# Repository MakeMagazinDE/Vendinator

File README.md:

Maker Media GmbH

***

# Verkaufsautomat mit ESP

### Eigene Waren zu vertreiben, kann ganz schön aufwendig sein. Mit einem selbst gebauten Automaten geht das ganz einfach. Einmal eingestellt, übernimmt er die Transaktionen und meldet Verkäufe und Fehler ans Smartphone. Man muss sich nur gut überlegen, wie Hard- und Software zusammenspielen sollen. Dann lässt sich sogar im Schlaf Geld verdienen.

Ergänzend zum Artikel in der Make 5/24 findet ihr hier die Sketches, Schaltpläne und Ablaufpläne.

Den vollständigen Artikel kann man in der **[Make-Ausgabe 5/24](https://www.heise.de/select/make/2024/5)** lesen.

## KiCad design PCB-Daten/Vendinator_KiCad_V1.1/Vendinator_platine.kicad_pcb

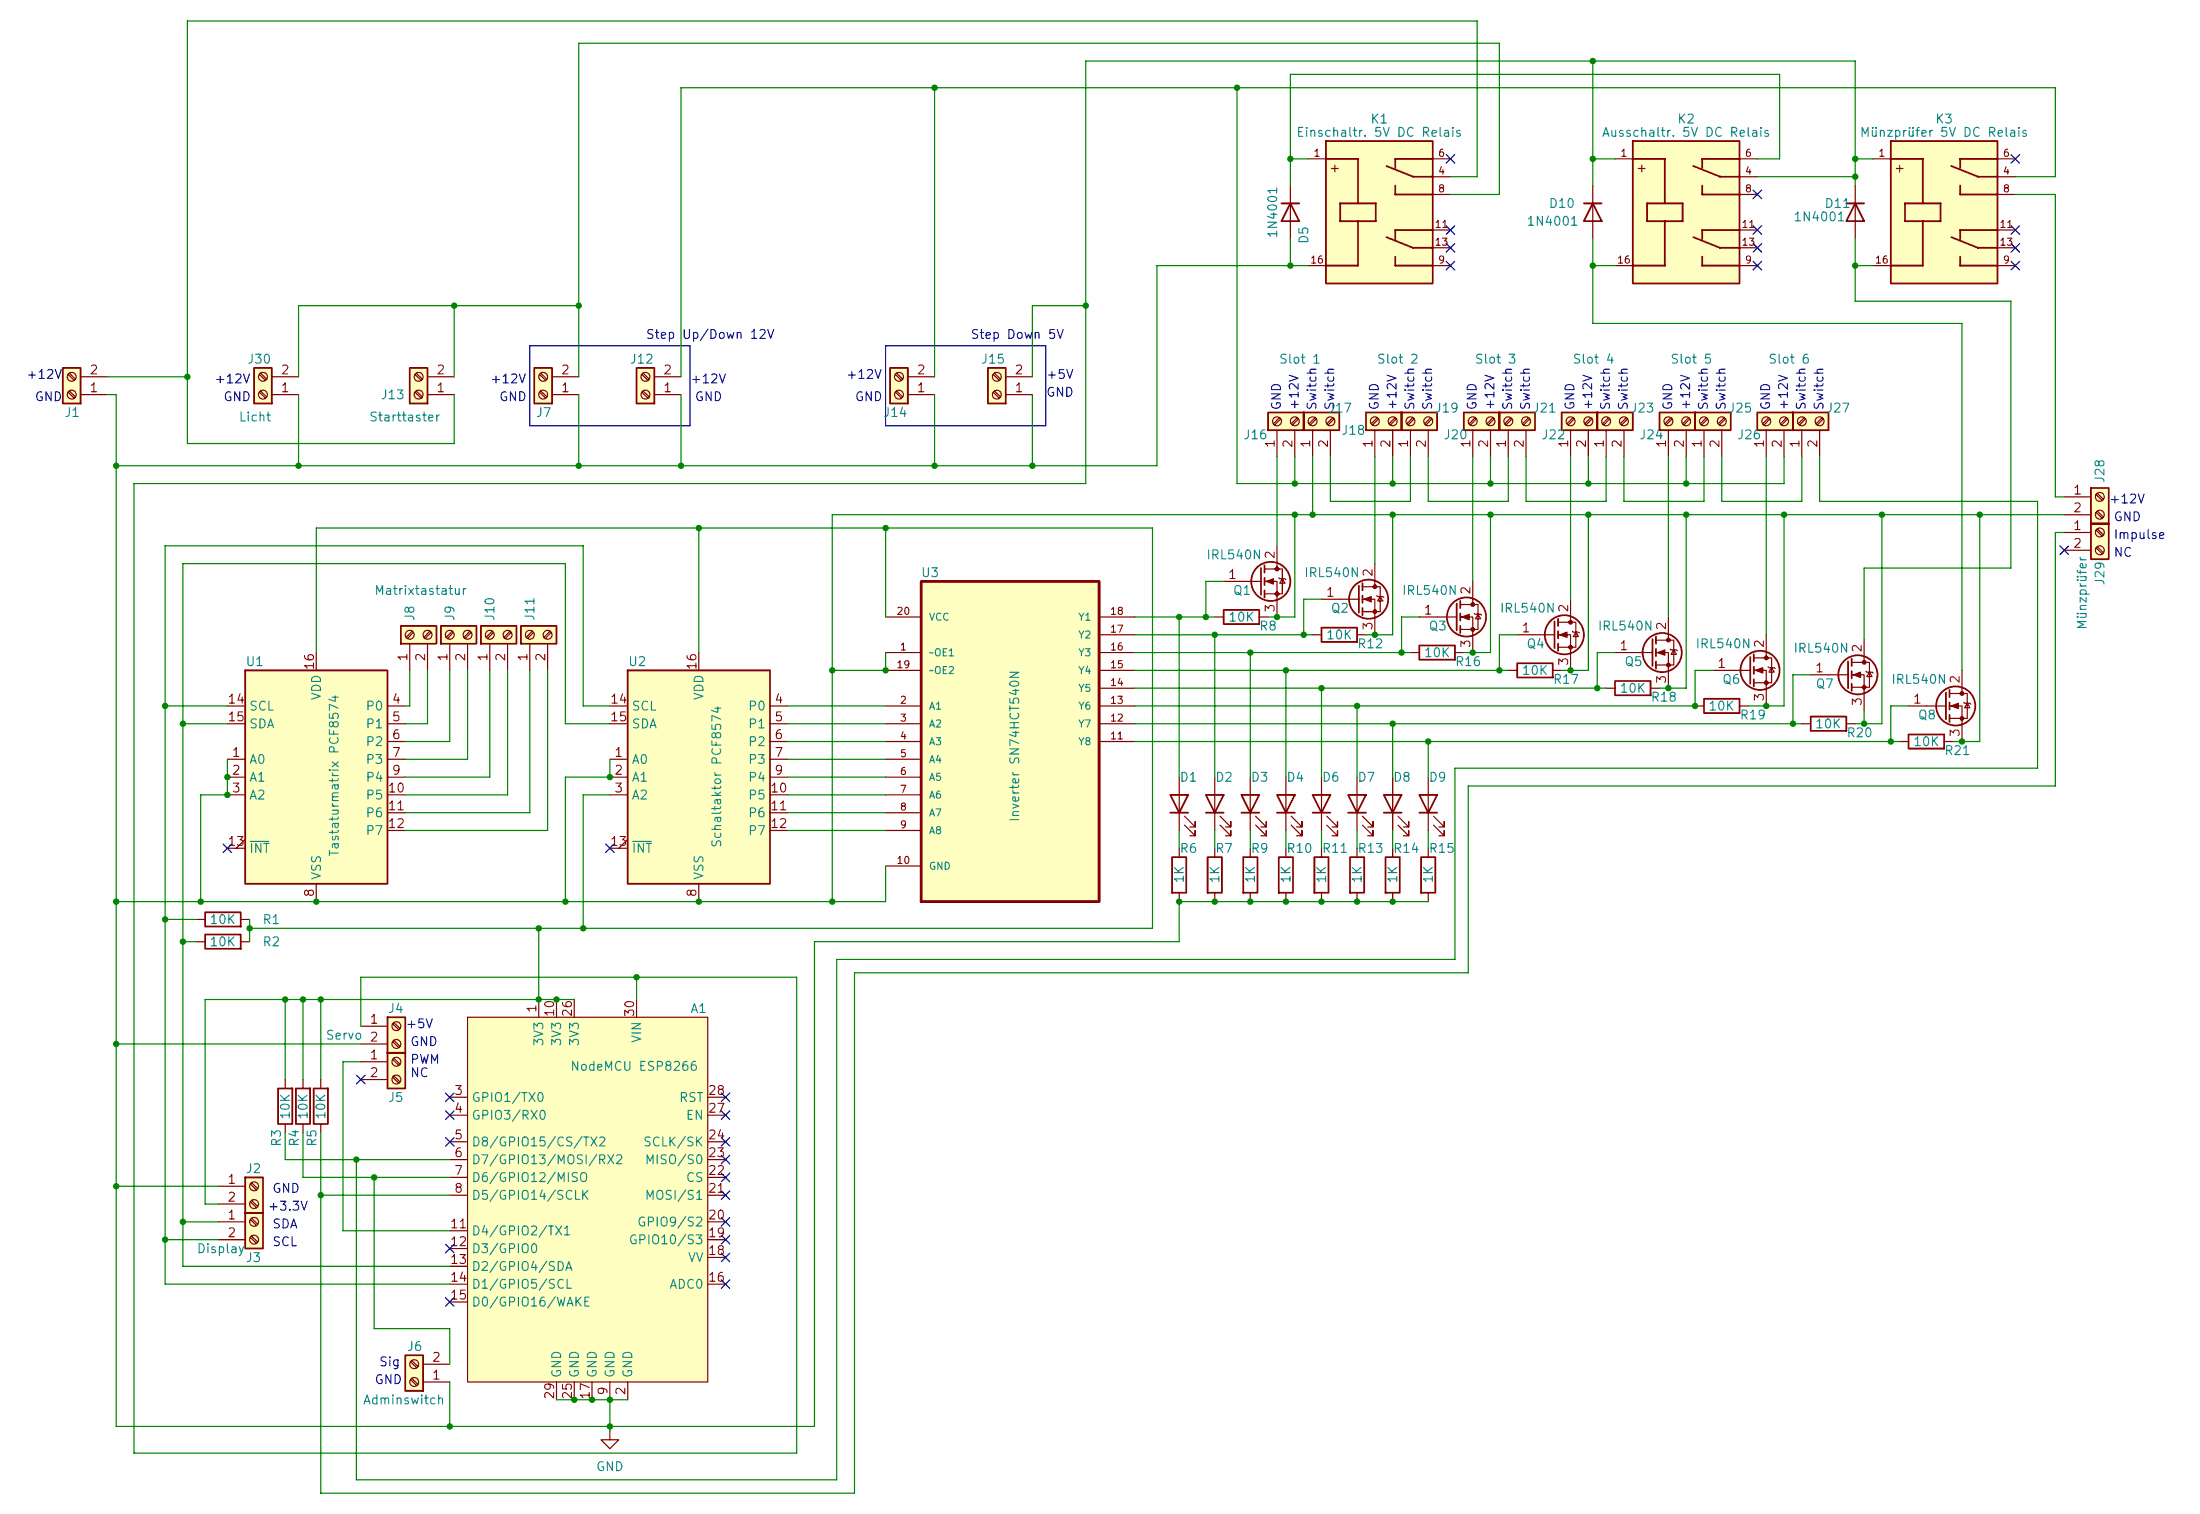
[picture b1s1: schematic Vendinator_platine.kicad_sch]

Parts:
A1: NodeMCU ESP8266; NodeMCU-LoLinV3_2
D1: LED grün; LED_D5.0mm
D2, D3, D4, D6, D7, D8, D9: LED; LED_D5.0mm
D5, D10, D11: 1N4001; D_DO-41_SOD81_P10.16mm_Horizontal
J1: Batterie IN; TerminalBlock_MetzConnect_Type011_RT05502HBWC_1x02_P5.00mm_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
J2: Display; TerminalBlock_MetzConnect_Type011_RT05502HBWC_1x02_P5.00mm_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
J3: Display 2; TerminalBlock_MetzConnect_Type011_RT05502HBWC_1x02_P5.00mm_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
J4: Servo; TerminalBlock_MetzConnect_Type011_RT05502HBWC_1x02_P5.00mm_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
J5: Servo 2; TerminalBlock_MetzConnect_Type011_RT05502HBWC_1x02_P5.00mm_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
J6: Adminswitch; TerminalBlock_MetzConnect_Type011_RT05502HBWC_1x02_P5.00mm_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
J7: 12V Step Up/Down IN; JUP_P20mm
J8: Matrixtastatur; TerminalBlock_MetzConnect_Type011_RT05502HBWC_1x02_P5.00mm_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
J9: Matrixtastatur 2; TerminalBlock_MetzConnect_Type011_RT05502HBWC_1x02_P5.00mm_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
J10: Matrixtastatur 3; TerminalBlock_MetzConnect_Type011_RT05502HBWC_1x02_P5.00mm_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
J11: Matrixtastatur 4; TerminalBlock_MetzConnect_Type011_RT05502HBWC_1x02_P5.00mm_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
J12: 12V Step Up/Down OUT; JUP_P20mm
J13: Starttaster; TerminalBlock_MetzConnect_Type011_RT05502HBWC_1x02_P5.00mm_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
J14: Step Down 5V IN; JUP_P20mm
J15: Step Down 5V OUT; JUP_P20mm
J16: Slot 1; TerminalBlock_MetzConnect_Type011_RT05502HBWC_1x02_P5.00mm_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
J17: Slotswitch 1; TerminalBlock_MetzConnect_Type011_RT05502HBWC_1x02_P5.00mm_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
J18: Slot 2; TerminalBlock_MetzConnect_Type011_RT05502HBWC_1x02_P5.00mm_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
J19: Slotswitch 2; TerminalBlock_MetzConnect_Type011_RT05502HBWC_1x02_P5.00mm_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
J20: Slot 3; TerminalBlock_MetzConnect_Type011_RT05502HBWC_1x02_P5.00mm_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
J21: Slotswitch 3; TerminalBlock_MetzConnect_Type011_RT05502HBWC_1x02_P5.00mm_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
J22: Slot 4; TerminalBlock_MetzConnect_Type011_RT05502HBWC_1x02_P5.00mm_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
J23: Slotswitch 4; TerminalBlock_MetzConnect_Type011_RT05502HBWC_1x02_P5.00mm_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
J24: Slot 5; TerminalBlock_MetzConnect_Type011_RT05502HBWC_1x02_P5.00mm_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
J25: Slotswitch 5; TerminalBlock_MetzConnect_Type011_RT05502HBWC_1x02_P5.00mm_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
J26: Slot 6; TerminalBlock_MetzConnect_Type011_RT05502HBWC_1x02_P5.00mm_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
J27: Slotswitch 6; TerminalBlock_MetzConnect_Type011_RT05502HBWC_1x02_P5.00mm_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
J28: Münzprüfer; TerminalBlock_MetzConnect_Type011_RT05502HBWC_1x02_P5.00mm_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
J29: Münzprüfer 2; TerminalBlock_MetzConnect_Type011_RT05502HBWC_1x02_P5.00mm_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
J30: Licht; TerminalBlock_MetzConnect_Type011_RT05502HBWC_1x02_P5.00mm_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
K1: Einschaltr. 5V DC Relais; SDS_Relay; PARTREV 0917
K2: Ausschaltr. 5V DC Relais; SDS_Relay; PARTREV 0917
K3: Münzprüfer 5V DC Relais; SDS_Relay; PARTREV 0917
Q1, Q2, Q3, Q4, Q5, Q6, Q7, Q8: IRL540N; TO-220-3_Vertical
R1, R2, R3, R4, R5, R8, R12, R16, R17, R18, R19, R20, R21: 10K; R_Axial_DIN0207_L6.3mm_D2.5mm_P10.16mm_Horizontal
R6, R7, R9, R10, R11, R13, R14, R15: 1K; R_Axial_DIN0207_L6.3mm_D2.5mm_P10.16mm_Horizontal
U1: Tastaturmatrix PCF8574; DIP-16_W7.62mm_Socket_LongPads
U2: Schaltaktor PCF8574; DIP-16_W7.62mm_Socket_LongPads
U3: Inverter SN74HCT540N; DIP-20_W7.62mm_Socket_LongPads; MPN SN74HCT540N

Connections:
GND: A1.2 (GND), A1.9 (GND), A1.17 (GND), A1.25 (GND), A1.29 (GND), D5.2 (A), J1.1, J2.1, J4.2, J6.1, J7.1, J12.1, J14.1, J15.1, J17.1, J28.2, J30.1, K1.16, Q1.3 (S), Q2.3 (S), Q3.3 (S), Q4.3 (S), Q5.3 (S), Q6.3 (S), Q7.3 (S), Q8.3 (S), R6.2, R7.2, R8.2, R9.2, R10.2, R11.2, R12.2, R13.2, R14.2, R15.2, R16.2, R17.2, R18.2, R19.2, R20.2, R21.2, U1.1 (A0), U1.2 (A1), U1.3 (A2), U1.8 (VSS), U2.1 (A0), U2.2 (A1), U2.8 (VSS), U3.1 (~OE1), U3.10 (GND), U3.19 (~OE2)
unnamed: A1.14 (D1/GPIO5/SCL), J3.2, R1.1, U1.14 (SCL), U2.14 (SCL)
unnamed: A1.13 (D2/GPIO4/SDA), J3.1, R2.1, U1.15 (SDA), U2.15 (SDA)
unnamed: A1.11 (D4/GPIO2/TX1), J5.1
unnamed: A1.8 (D5/GPIO14/SCLK), J29.1, R5.1
unnamed: A1.7 (D6/GPIO12/MISO), J6.2, R4.1
unnamed: A1.6 (D7/GPIO13/MOSI/RX2), J27.2, R3.1
unnamed: A1.30 (VIN), D10.1 (K), D11.1 (K), J4.1, J15.2, K2.1, K2.4, K3.1
unnamed: D1.2 (A), Q1.1 (G), R8.1, U3.18 (Y1)
unnamed: D1.1 (K), R6.1
unnamed: D2.2 (A), Q2.1 (G), R12.1, U3.17 (Y2)
unnamed: D2.1 (K), R7.1
unnamed: D3.2 (A), Q3.1 (G), R16.1, U3.16 (Y3)
unnamed: D3.1 (K), R9.1
unnamed: D4.2 (A), Q4.1 (G), R17.1, U3.15 (Y4)
unnamed: D4.1 (K), R10.1
unnamed: D5.1 (K), K1.1, K2.6
unnamed: D6.2 (A), Q5.1 (G), R18.1, U3.14 (Y5)
unnamed: D6.1 (K), R11.1
unnamed: D7.2 (A), Q6.1 (G), R19.1, U3.13 (Y6)
unnamed: D7.1 (K), R13.1
unnamed: D8.2 (A), Q7.1 (G), R20.1, U3.12 (Y7)
unnamed: D8.1 (K), R14.1
unnamed: D9.2 (A), Q8.1 (G), R21.1, U3.11 (Y8)
unnamed: D9.1 (K), R15.1
unnamed: D10.2 (A), K2.16, Q8.2 (D)
unnamed: D11.2 (A), K3.16, Q7.2 (D)
unnamed: J1.2, J13.1, K1.4
unnamed: A1.1 (3V3), A1.10 (3V3), A1.26 (3V3), J2.2, R1.2, R2.2, R3.2, R4.2, R5.2, U1.16 (VDD), U2.3 (A2), U2.16 (VDD), U3.20 (VCC)
unnamed: J8.1, U1.4 (P0)
unnamed: J8.2, U1.5 (P1)
unnamed: J9.1, U1.6 (P2)
unnamed: J9.2, U1.7 (P3)
unnamed: J10.1, U1.9 (P4)
unnamed: J10.2, U1.10 (P5)
unnamed: J11.1, U1.11 (P6)
unnamed: J11.2, U1.12 (P7)
unnamed: J12.2, J14.2, J16.2, J18.2, J20.2, J22.2, J24.2, J26.2, K3.4
unnamed: J7.2, J13.2, J30.2, K1.8
unnamed: J16.1, Q1.2 (D)
unnamed: J17.2, J19.1
unnamed: J18.1, Q2.2 (D)
unnamed: J19.2, J21.1
unnamed: J20.1, Q3.2 (D)
unnamed: J21.2, J23.1
unnamed: J22.1, Q4.2 (D)
unnamed: J23.2, J25.1
unnamed: J24.1, Q5.2 (D)
unnamed: J25.2, J27.1
unnamed: J26.1, Q6.2 (D)
unnamed: J28.1, K3.8
unnamed: U2.4 (P0), U3.2 (A1)
unnamed: U2.5 (P1), U3.3 (A2)
unnamed: U2.6 (P2), U3.4 (A3)
unnamed: U2.7 (P3), U3.5 (A4)
unnamed: U2.9 (P4), U3.6 (A5)
unnamed: U2.10 (P5), U3.7 (A6)
unnamed: U2.11 (P6), U3.8 (A7)
unnamed: U2.12 (P7), U3.9 (A8)

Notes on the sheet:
Switch
Impulse
GND
+5V
+12V
+12V
SCL
SDA
+3.3V
Step Down 5V
GND
PWM
Sig
Step Up/Down 12V

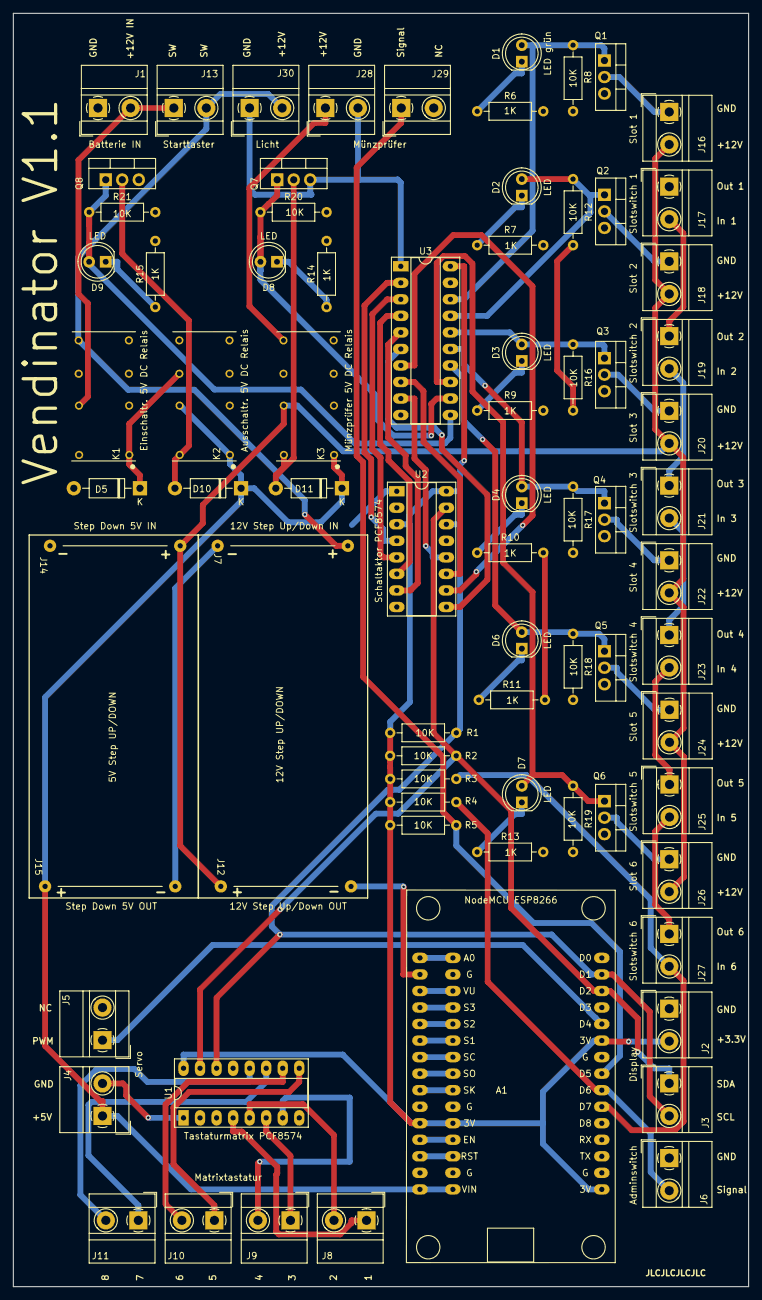
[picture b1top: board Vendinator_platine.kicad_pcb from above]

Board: 2 copper layers, 113.0 x 195.6 mm, 77 parts (0 on the bottom side), 59 nets.
